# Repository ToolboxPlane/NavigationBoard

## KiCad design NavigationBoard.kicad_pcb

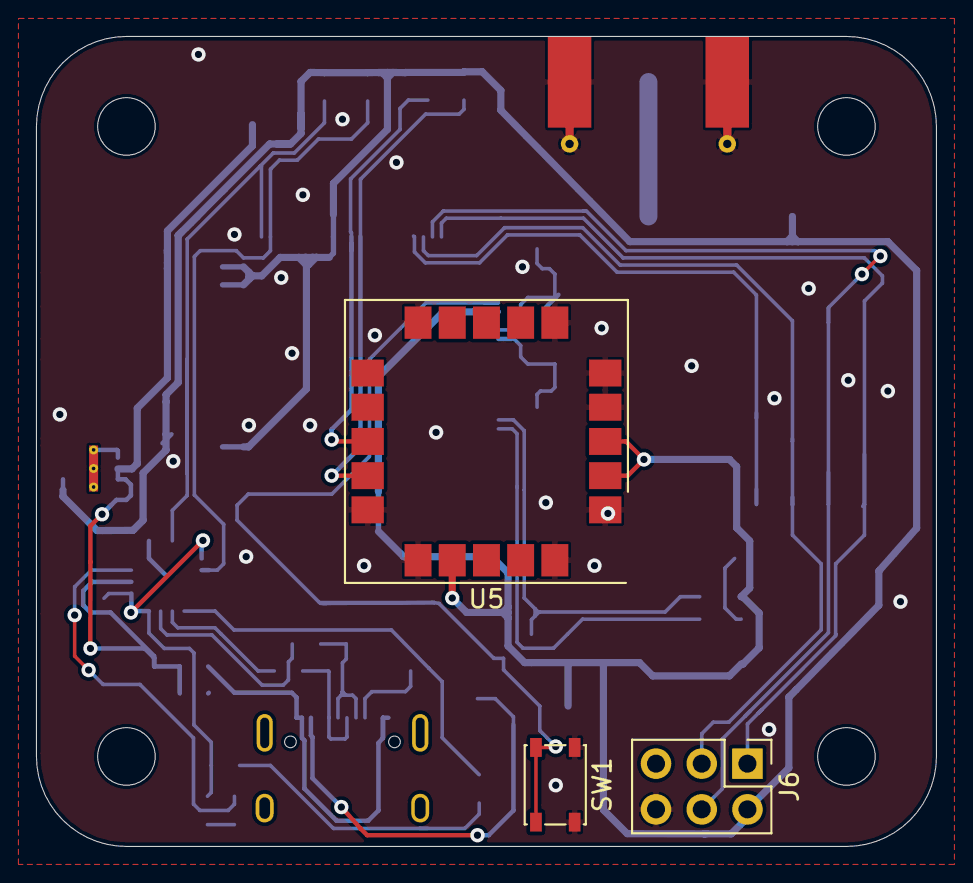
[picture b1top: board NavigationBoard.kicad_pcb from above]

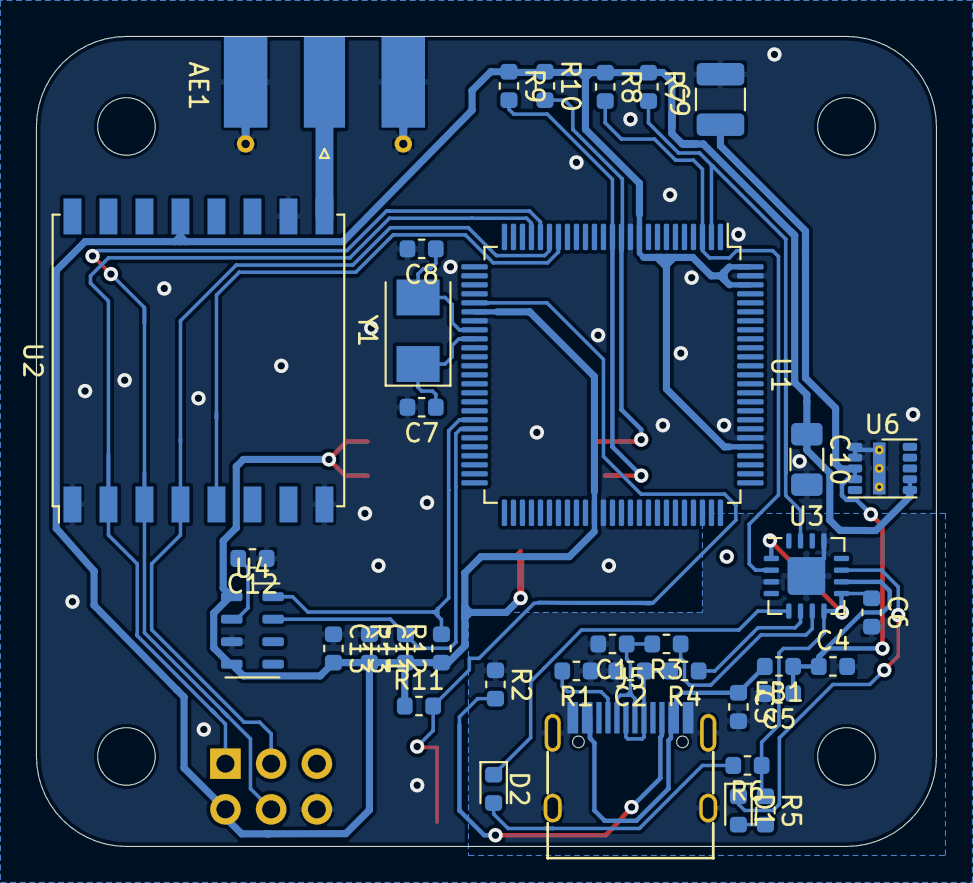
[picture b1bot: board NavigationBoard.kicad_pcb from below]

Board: 2 copper layers, 50.0 x 45.0 mm, 44 parts (37 on the bottom side), 31 nets.

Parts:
AE1: Antenna_Shield; SMA_Molex_73251-1153_EdgeMount_Horizontal
C1, C2: 47p; C_0603_1608Metric
C3: 10nF; C_0603_1608Metric
C4, C6, C12, C13: 100nF; C_0603_1608Metric
C5: 4.7µF; C_0603_1608Metric
C7, C8: 8pF; C_0603_1608Metric
C9: 10µF; C_1210_3225Metric
C10: 22µF; C_1206_3216Metric
C11: 10µF; C_0603_1608Metric
D1, D2: LED_Small; LED_0603_1608Metric
FB1: 600 Ohms @ 100MHz; C_0603_1608Metric
H1, H2, H3, H4: MountingHole; MountingHole_3.2mm_M3
J5: USB_C_Receptacle_USB2.0; USB_C_Receptacle_GT-USB-7010
J6: AVR-ISP-6; PinHeader_2x03_P2.54mm_Vertical
R1, R2: 5.1k; R_0603_1608Metric
R3, R4: 27; R_0603_1608Metric
R5, R6: 270; R_0603_1608Metric
R7, R8, R9, R10, R11, R12, R13: 10k; R_0603_1608Metric
SW1: SW_Push; SW_SPST_PTS810
U1: ATmega2560-16AU; TQFP-100_14x14mm_P0.5mm
U2: RFM96W-433S2; HOPERF_RFM9XW_SMD
U3: FT230XQ; QFN-16-1EP_4x4mm_P0.65mm_EP2.1x2.1mm
U4: MPL3115A2; NXP_LGA-8_3x5mm_P1.25mm_H1.1mm
U5: ublox_SAM-M8Q
U6: LMZM23600V3; Texas_SIL0010A_MicroSiP-10-1EP_3.8x3mm_P0.6mm_EP0.7x2.9mm_T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
Y1: 16MHz; Crystal_SMD_5032-2Pin_5.0x3.2mm

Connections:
+3V3: C10.1, C11.2, C13.2, J6.2, R7.1, R8.1, R9.1, R10.1, R11.1, R12.1, R13.1, U1.10, U1.31, U1.61, U1.80, U1.98, U1.100, U2.13, U4.1, U4.4, U5.2, U5.3, U5.17, U6.6, U6.7
+5V: C4.1, C5.1, C9.1, FB1.1, U3.10, U6.3, U6.4
/MISO: J6.1, U1.22, U2.2
/MOSI: J6.4, U1.21, U2.3
/RXD0: R7.2, U1.2, U3.15
/RXD2: R10.2, U1.12, U5.13
/SCK: J6.3, U1.20, U2.4
/SCL: R12.2, U1.43, U4.8
/SDA: R13.2, U1.44, U4.7
/TXD0: R8.2, U1.3, U3.2
/TXD2: R9.2, U1.13, U5.14
/~RESET: R11.2, SW1.2, U1.30
/~SS: U1.19, U2.5
GND: AE1.2, C7.2, C8.2, C9.2, C10.2, C11.1, C12.1, C13.1, J6.6, SW1.1, U1.11, U1.32, U1.62, U1.81, U1.99, U2.1, U2.8, U2.10, U4.3, U5.1, U5.4, U5.5, U5.6, U5.10, U5.11, U5.15, U5.16, U5.20, U6.1, U6.2, U6.11
GNDS: C1.2, C2.2, C3.2, C4.2, C5.2, C6.2, J5.A1, J5.A12, J5.B1, J5.B12, J5.S1, R1.1, R2.1, U3.3, U3.13, U3.17
unnamed: AE1.1, U2.9
unnamed: C1.1, J5.A7, J5.B7, R3.2
unnamed: C2.1, J5.A6, J5.B6, R4.2
unnamed: C6.1, R5.1, R6.1, U3.1, U3.8, U3.9
unnamed: C7.1, U1.34, Y1.1
unnamed: C8.1, U1.33, Y1.2
unnamed: C12.2, U4.2
unnamed: D1.1, U3.11
unnamed: D1.2, R5.2
unnamed: D2.1, U3.5
unnamed: D2.2, R6.2
unnamed: J5.A5, R1.2
unnamed: J5.B5, R2.2
unnamed: R3.1, U3.7
unnamed: R4.1, U3.6
VBUS: C3.1, FB1.2, J5.A4, J5.A9, J5.B4, J5.B9

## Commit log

2018-10-21 Added GPS
2018-10-21 Added gitignore
2018-10-21 Added Barometer
2018-10-21 Added LoRa
2018-10-21 Added Connectors for HC-SR04, UART3 and I2C
2018-10-21 First draft of the layout finished
2019-04-26 kicad und so
2019-04-26 ft230 annotation
2020-03-30 KiCad gitignore, add project file
2020-03-30 remove L86, fix Lora symbol
2020-03-30 update FT230 submodule
2020-03-30 3V regulator, crystal oscillator, reset switch, new GPS
2020-03-30 update ft230
2020-03-30 add ISP, MPL3115A2
2020-07-27 no clue, this has been >4 months and diff is kinda useless here...
2020-07-28 Erster Grober Entwurf
2020-07-28 Kleinerer AVR-ISP Stecker
2020-07-30 Layout weiter gemacht
2020-08-01 Weniger Leiterbahnen auf der Oberseite
2020-08-03 XT 30 entfernt
